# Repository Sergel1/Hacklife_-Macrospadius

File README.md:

# Hacklife_-Macrospadius
My first ever project with a pcb design and first hackclub activity
The idea of the project is to complete the 10 week "course" of halflife by hackclub
for the first week i decided to build a macropad since it was farily simple and there was a hackclub tutorial
_______________________________________________________________________________________________________________

I call the macropad : Macrpadilius
Macrpadilius is a custom six-key macropad designed in KiCad. It uses a Seeed Studio XIAO, six Cherry MX-compatible switches, an EC11 rotary encoder with a push button, and a 0.91-inch I2C OLED display.

![Finishedbuild](assets/full_build_macropadilius.jpeg
)

Features:    Six programmable mechanical keys
             EC11 rotary encoder
            Encoder push-button input
             0.91-inch I2C OLED display
            Seeed Studio XIAO microcontroller
            USB-C connection
           Cherry MX-compatible switch footprints
           Custom PCB shape
           B.Cu ground plane
           KiCad source files included

           Project Status
The PCB is currently under development.

Schematic completed - done
Components assigned to footprints- done
PCB routed - done
Ground zone added - done
Electrical Rules Check completed - done
Design Rules Check completed - done
Mounting holes added - done
Physical footprints verified - not yet
Gerber files generated - not yet
PCB ordered - not yet
Firmware completed  - not yet
Final board assembled and tested- Not yet
PCB Preview

PCB Editor
![PCB-editor](assets/PCB.Editor.png
)

Front 3D view
![Front 3D view](assets/PCB-3d-front.png
)
Back 3D view
![Back 3D view](assets/PCB-3d-back.png
)
Schematic
![Schematic](assets/schematic.png
)
The buttons are connected between individual GPIO pins and GND. The firmware will use the microcontroller's internal pull-up resistors.

The OLED uses I2C:

VCC to 3.3 V
GND to GND
SDA to the XIAO SDA pin
SCL to the XIAO SCL pin
The rotary encoder uses:

A to a GPIO pin
B to a separate GPIO pin
C to GND
S1 to a GPIO pin
S2 to GND
Bill of Materials
Quantity	Component	Description
1	Seeed Studio XIAO	Exact model: Seeed Studio XIAO RP2040 Plus
6	Mechanical switches	Cherry MX-compatible PCB-mount switches -  Vendor 
6	Keycaps	Standard 1U keycaps
1	Rotary encoder	EC11-compatible encoder with push button
1	Encoder knob	Knob matching the encoder shaft
1	OLED display	0.91-inch I2C OLED
1	Custom PCB	Two-layer PCB
2 or 4	M2 screws	For mounting the PCB
2 or 4	M2 standoffs	Height depends on the enclosure
Hardware Files
The KiCad project files are located in the hardware/ directory.

Macrpadilius.kicad_pro
Macrpadilius.kicad_sch
Macrpadilius.kicad_pcb
Firmware
The firmware will support:

Six programmable keys
Rotary encoder clockwise and counterclockwise inputs
Rotary encoder push button
OLED status information
Multiple macropad layers or modes
Firmware development has not been completed yet.

Manufacturing
Before manufacturing, verify:

The exact EC11 encoder dimensions
OLED module dimensions and pin order
XIAO footprint and USB-C orientation
Cherry MX switch compatibility
Keycap and encoder-knob clearance
Mounting-hole locations
Copper-to-edge clearance
DRC results
Gerber and drill-file output
Do not manufacture the PCB before comparing every footprint with the exact physical component or its mechanical drawing.

Assembly
Planned assembly order:

Inspect the manufactured PCB.
Test continuity between power and GND.
Solder the Seeed Studio XIAO or its sockets.
Solder the OLED header.
Solder the rotary encoder.
Install and solder the six switches.
Inspect every solder joint.
Connect the board through USB-C.
Upload test firmware.
Test every switch, encoder signal, and OLED connection.
Designed With
KiCad
Arduino IDE or PlatformIO
Seeed Studio XIAO
GitHub
License
A license has not been selected yet.

Possible options include:

MIT License for firmware
CERN Open Hardware Licence Version 2 for PCB hardware
Creative Commons for documentation and images
Author
Created by Sergel Hasabella

tl;dr, This project being made is a a 6 button macropad with screen and a knob (7th), most of the work is done and uploaded

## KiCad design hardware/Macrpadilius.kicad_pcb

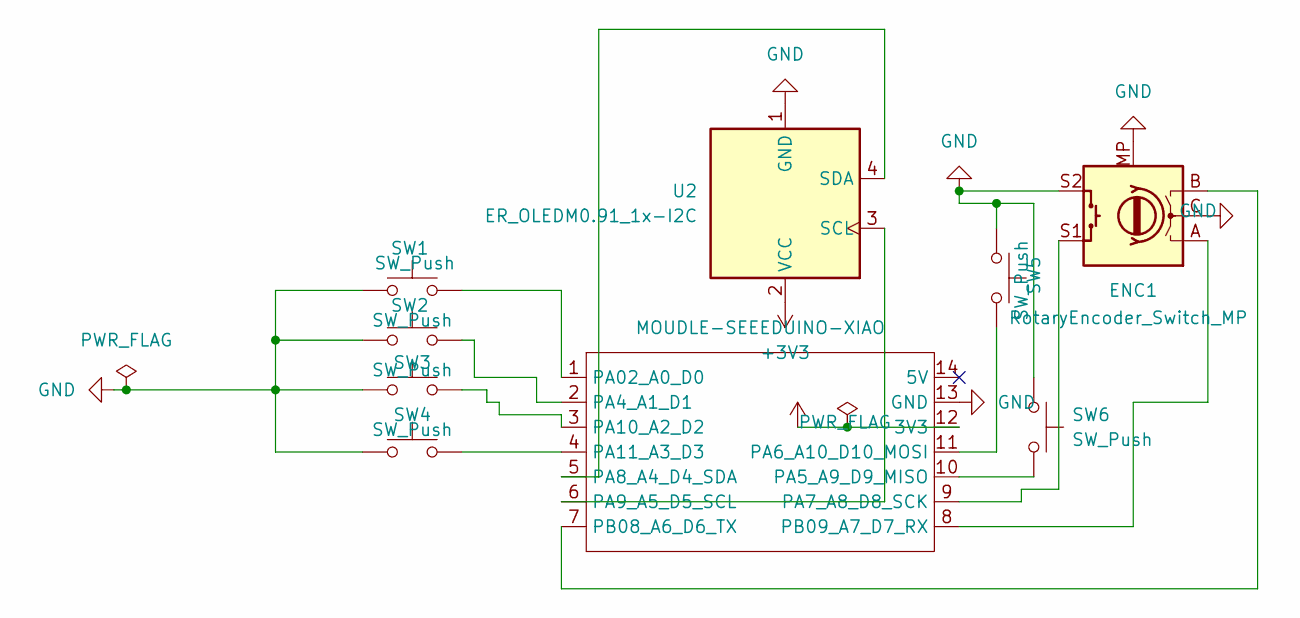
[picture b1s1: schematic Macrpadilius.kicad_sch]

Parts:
ENC1: RotaryEncoder_Switch_MP; RotaryEncoder_Alps_EC11E-Switch_Vertical_H20mm
SW1, SW2, SW3, SW4, SW5, SW6: SW_Push; SW_Cherry_MX_1.00u_PCB
U1: MOUDLE-SEEEDUINO-XIAO; XIAO-Generic-Hybrid-14P-2.54-21X17.8MM
U2: ER_OLEDM0.91_1x-I2C

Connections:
+3V3: U1.12 (3V3), U2.2 (VCC)
GND: ENC1.C, ENC1.MP, ENC1.S2, SW1.1, SW2.1, SW3.1, SW4.1, SW5.1, SW6.1, U1.13 (GND), U2.1 (GND)
unnamed: SW1.2, U1.1 (PA02_A0_D0)
unnamed: SW2.2, U1.2 (PA4_A1_D1)
unnamed: SW6.2, U1.10 (PA5_A9_D9_MISO)
unnamed: SW5.2, U1.11 (PA6_A10_D10_MOSI)
unnamed: ENC1.S1, U1.9 (PA7_A8_D8_SCK)
unnamed: U1.5 (PA8_A4_D4_SDA), U2.4 (SDA)
unnamed: U1.6 (PA9_A5_D5_SCL), U2.3 (SCL)
unnamed: SW3.2, U1.3 (PA10_A2_D2)
unnamed: SW4.2, U1.4 (PA11_A3_D3)
unnamed: ENC1.B, U1.7 (PB08_A6_D6_TX)
unnamed: ENC1.A, U1.8 (PB09_A7_D7_RX)

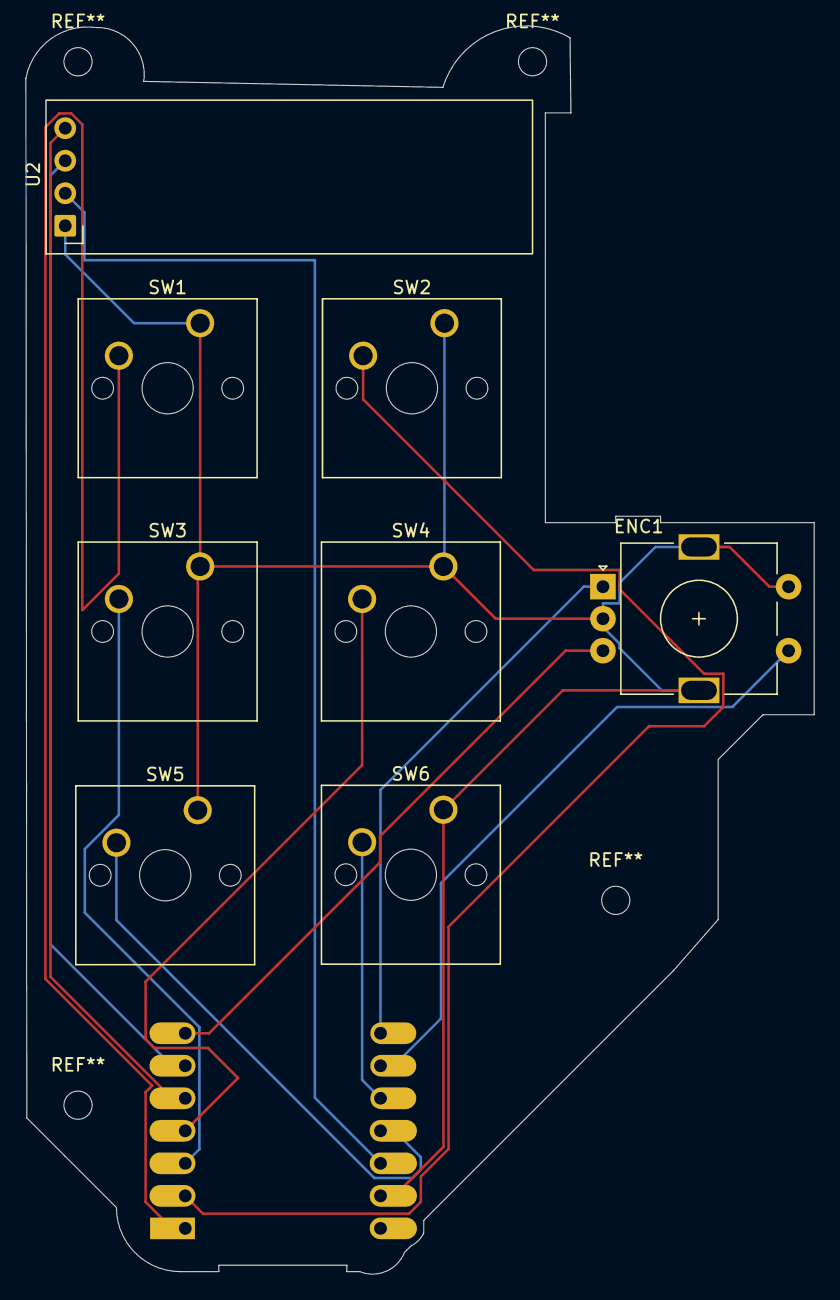
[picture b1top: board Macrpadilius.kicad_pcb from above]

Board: 2 copper layers, 61.6 x 97.5 mm, 9 parts (1 on the bottom side), 13 nets.

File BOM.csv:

Item,Qty,Supplier,Cost/item,Total Cost,link
RotaryEncoder_Switch_MP,1,aliexpress,$2.70,$2.70,https://www.aliexpress.com/item/1005013194256936.html?spm=a2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
SW_Push,10,aliexpress,$0.38,$3.80,https://www.aliexpress.com/item/1005009541679897.html?spm=a2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
MOUDLE-SEEEDUINO-XIAO,1,seeedstudio,$7.53,$7.53,https://www.aliexpress.com/item/1005012441490478.html?spm=a2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
ER_OLEDM0.96_1x-I2C,1,aliexpress,$3.52,$3.52,https://www.aliexpress.com/item/1005009170035050.html?spm=a2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
pcb,1,jlcpcb,$7.50,$7.50,https://trade.jlcpcb.com/checkout/payMethod/?unionSettleId=5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
Estimated total shipping,1,,,$4.94,
